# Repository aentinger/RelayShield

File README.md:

💾 Relay Shield
===============

# 📸 Image

# 📂 Description

The LXRobotics Relay Shield allows to independently switch up to different 4 loads. The switching of any relay is signalised by its own red status LED. High quality screw terminals ensure stable and durable connections. For an quick and easy start, a open source Arduino library with sample programs is available.

**Features**

* Potential-free switching of up to 4 different loads through 4 relays/contactors
* Max. current per relay: 10 A
* Max. voltage DC per relay: 24 V DC
* Max voltage AC per relay: 250 V AC
* Relay type: SPDT (Single Pole commutator)
* Red LED's shows relay status (ON/OFF)
* Optocouplers used to isolate relay circuit from Arduino 
* High quality screw terminals
* Arduino Library with example programs is available on GitHub

# 🎥 [Video](images/relay_shield_demo.mp4)

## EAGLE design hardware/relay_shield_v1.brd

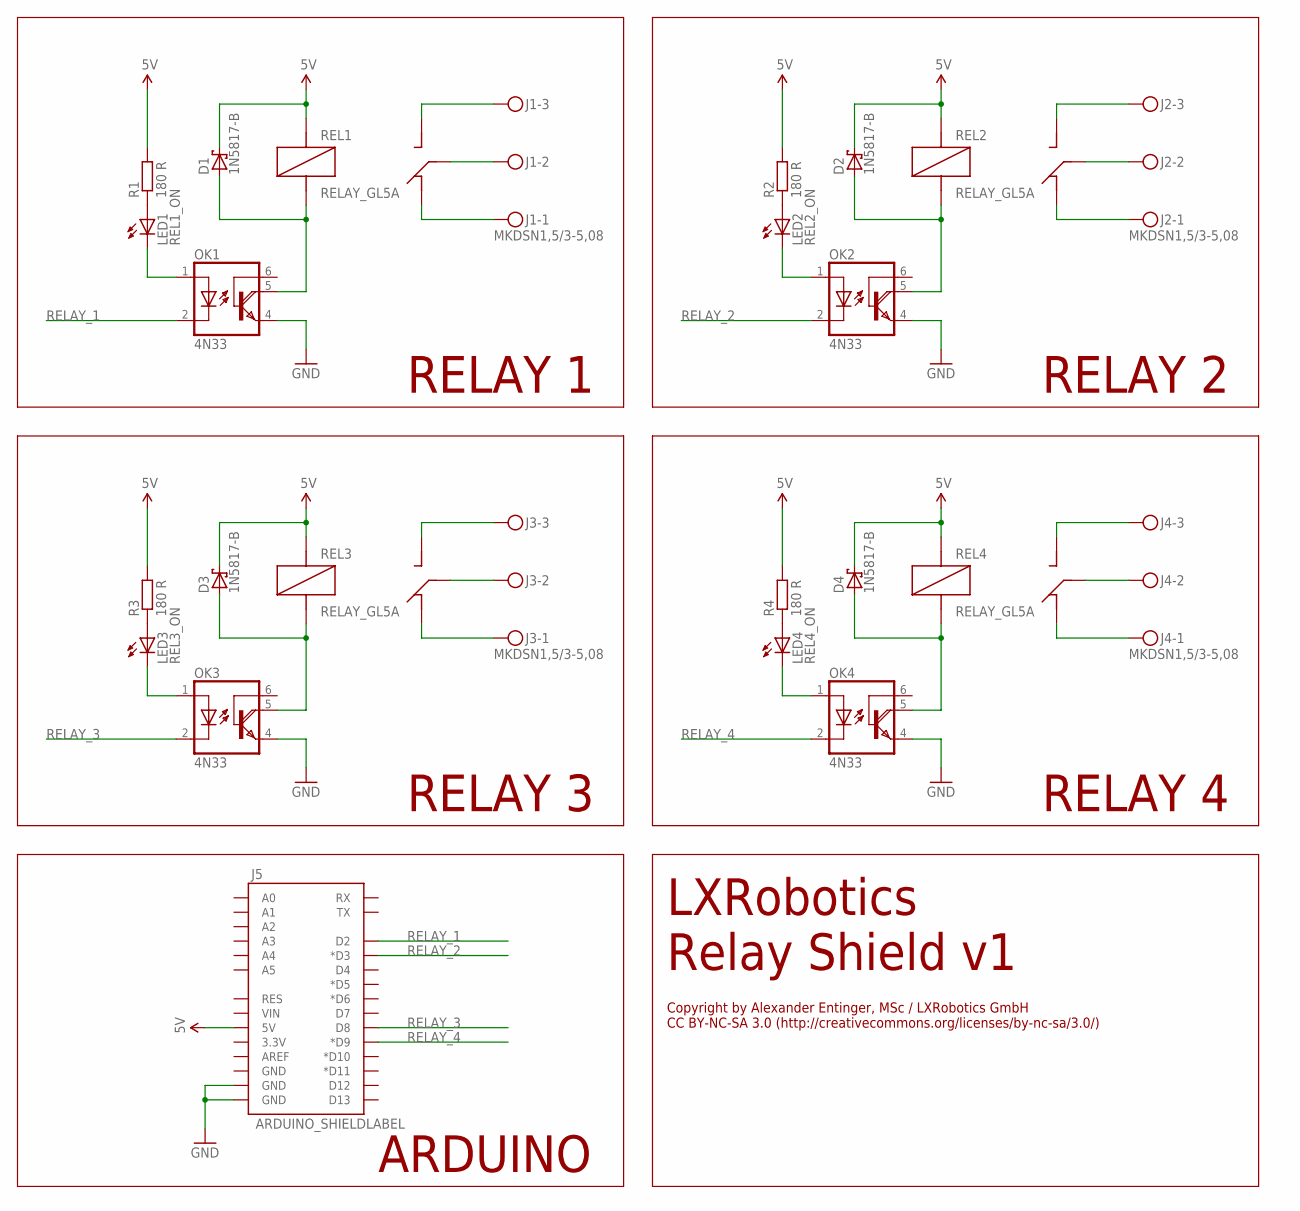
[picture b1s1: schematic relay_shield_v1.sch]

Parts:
D1, D2, D3, D4: 1N5817-B; DO41-7.6
J1, J2, J3, J4: MKDSN1,5/3-5,08
J5: ARDUINO_SHIELDLABEL; DUEMILANOVE_SHIELD
LED1: REL1_ON; LED5MM
LED2: REL2_ON; LED5MM
LED3: REL3_ON; LED5MM
LED4: REL4_ON; LED5MM
OK1, OK2, OK3, OK4: 4N33; DIL06
R1, R2, R3, R4: 180 R; 0204/7
REL1, REL2, REL3, REL4: RELAY_GL5A

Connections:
5V: D1.C, D2.C, D3.C, D4.C, J5.5V, R1.2, R2.2, R3.2, R4.2, REL1.R2 (R2_COIL1), REL2.R2 (R2_COIL1), REL3.R2 (R2_COIL1), REL4.R2 (R2_COIL1)
GND: J5.GND@0 (GND), J5.GND@1 (GND), OK1.4 (E), OK2.4 (E), OK3.4 (E), OK4.4 (E)
unnamed: D1.A, OK1.5 (COL), REL1.R5 (R5_COIL2)
unnamed: J1.2, REL1.R1 (R1_COMMON)
unnamed: J1.1, REL1.R4 (R4_SW)
unnamed: LED1.K (C), OK1.1 (A)
unnamed: LED1.A, R1.1
unnamed: J1.3, REL1.R3 (R3_SW)
unnamed: D2.A, OK2.5 (COL), REL2.R5 (R5_COIL2)
unnamed: LED2.K (C), OK2.1 (A)
unnamed: LED2.A, R2.1
unnamed: J2.2, REL2.R1 (R1_COMMON)
unnamed: J2.1, REL2.R4 (R4_SW)
unnamed: J2.3, REL2.R3 (R3_SW)
unnamed: D3.A, OK3.5 (COL), REL3.R5 (R5_COIL2)
unnamed: LED3.K (C), OK3.1 (A)
unnamed: LED3.A, R3.1
unnamed: J3.2, REL3.R1 (R1_COMMON)
unnamed: J3.1, REL3.R4 (R4_SW)
unnamed: J3.3, REL3.R3 (R3_SW)
unnamed: D4.A, OK4.5 (COL), REL4.R5 (R5_COIL2)
unnamed: LED4.K (C), OK4.1 (A)
unnamed: LED4.A, R4.1
unnamed: J4.2, REL4.R1 (R1_COMMON)
unnamed: J4.1, REL4.R4 (R4_SW)
unnamed: J4.3, REL4.R3 (R3_SW)
RELAY_1: J5.D2, OK1.2 (C)
RELAY_2: J5.D3 (*D3), OK2.2 (C)
RELAY_3: J5.D8, OK3.2 (C)
RELAY_4: J5.D9 (*D9), OK4.2 (C)

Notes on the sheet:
RELAY 1
RELAY 2
RELAY 3
RELAY 4
ARDUINO
LXRobotics Relay Shield v1
Copyright by Alexander Entinger, MSc / LXRobotics GmbH CC BY-NC-SA 3.0 (http://creativecommons.org/licenses/by-nc-sa/3.0/)

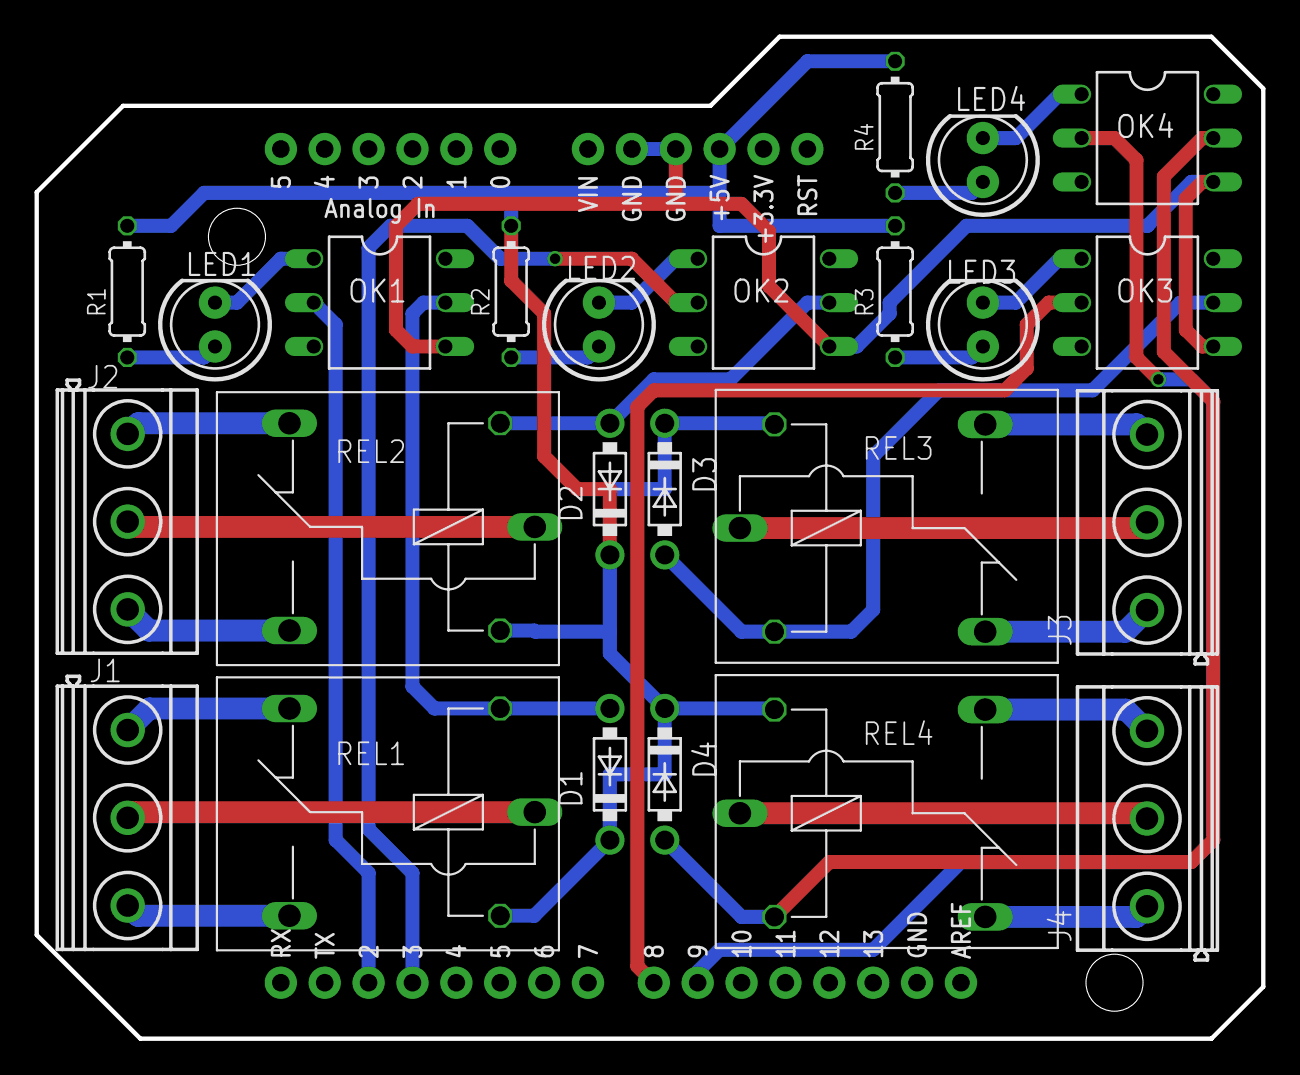
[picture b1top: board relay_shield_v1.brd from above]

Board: 2 copper layers, 71.0 x 58.0 mm, 25 parts (0 on the bottom side), 30 nets.

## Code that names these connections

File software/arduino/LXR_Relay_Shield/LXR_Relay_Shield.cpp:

/**
 * @author Alexander Entinger, MSc / LXRobotics
 * @brief this module implements the library for controlling the LXRobotics Relay Shield
 * @file LXR_Relay_Shield.cpp
 * @license Attribution-NonCommercial-ShareAlike 3.0 Unported (CC BY-NC-SA 3.0) ( http://creativecommons.org/licenses/by-nc-sa/3.0/ )
 */

#include "LXR_Relay_Shield.h"

static int const RELAY_1_PIN = 2;
static int const RELAY_2_PIN = 3;
static int const RELAY_3_PIN = 8;
static int const RELAY_4_PIN = 9;

/**
 * @brief initializes the LXR_Relay_Shield library
 */
void LXR_Relay_Shield::begin() {
  pinMode(RELAY_1_PIN, OUTPUT);
  pinMode(RELAY_2_PIN, OUTPUT);
  pinMode(RELAY_3_PIN, OUTPUT);
  pinMode(RELAY_4_PIN, OUTPUT);
  LXR_Relay_Shield::turn_off(REL1);
  LXR_Relay_Shield::turn_off(REL2);
  LXR_Relay_Shield::turn_off(REL3);
  LXR_Relay_Shield::turn_off(REL4);
}

/**
 * @brief turn a speficic relay on
 */
void LXR_Relay_Shield::turn_on(E_RELAY_SELECT const sel) {
  switch(sel) {
   case REL1: digitalWrite(RELAY_1_PIN, LOW); break; 
   case REL2: digitalWrite(RELAY_2_PIN, LOW); break;
   case REL3: digitalWrite(RELAY_3_PIN, LOW); break;
   case REL4: digitalWrite(RELAY_4_PIN, LOW); break;
   default: break;
  }
}

/**
 * @brief turn a speficic relay off
 */
void LXR_Relay_Shield::turn_off(E_RELAY_SELECT const sel) {
  switch(sel) {
   case REL1: digitalWrite(RELAY_1_PIN, HIGH); break; 
   case REL2: digitalWrite(RELAY_2_PIN, HIGH); break;
   case REL3: digitalWrite(RELAY_3_PIN, HIGH); break;
   case REL4: digitalWrite(RELAY_4_PIN, HIGH); break;
   default: break;
  }  
}

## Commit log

2014-06-04 initial checkin of relay shield files
2014-06-05 turns all relays off now at initialization of library
2014-06-06 adding beatbox and serial relay control examples
2014-06-06 inserted small protcol documentation into serial_relay_control.ino
2017-06-27 Adding hardware + images
2025-03-26 Add BOM.
2025-03-26 Add demo video.
2025-03-26 Pretty up README.

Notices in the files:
README.md:
License: CC BY-NC-SA 4.0
parts and their libraries:
SparkFun-LED: Licensing: CC v3.0 Share-Alike You are welcome to use this library for commercial purposes.
